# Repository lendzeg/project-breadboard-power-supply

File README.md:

# Breadboard Power Supply

This project is a breadboard power supply designed using KiCad. It provides stable and adjustable voltage outputs for prototyping and testing circuits on a breadboard. The design includes components such as voltage regulators (LM317 and LM7805), capacitors, resistors, connectors, and more.

## Features
- **Dual Voltage Outputs**:
  - Adjustable output voltage using the LM317 regulator.
  - Fixed 5V output using the LM7805 regulator.
- **Barrel Jack Input**:
  - Accepts a standard DC barrel jack for power input.
- **Screw Terminals**:
  - Easy connection for input and output wires.
- **LED Indicator**:
  - Power-on LED to indicate when the supply is active.
- **Compact Design**:
  - Optimized for use with breadboards and prototyping.

---

---

## Components List
| Reference | Value       | Footprint                                                                 |
|-----------|-------------|---------------------------------------------------------------------------|
| C1        | 10u         | Capacitor_THT:C_Disc_D3.0mm_W1.6mm_P2.50mm                                |
| C2        | 1u          | Capacitor_THT:C_Disc_D3.0mm_W1.6mm_P2.50mm                                |
| C3        | 0.1u        | Capacitor_THT:C_Disc_D3.0mm_W1.6mm_P2.50mm                                |
| D1        | LED         | LED_THT:LED_D5.0mm                                                        |
| J1        | Barrel_Jack | Connector_BarrelJack:BarrelJack_Horizontal                                |
| J2, J5    | Screw_Terminal_01x02 | TerminalBlock:TerminalBlock_bornier-2_P5.08mm                             |
| J4, J6    | Conn_01x02_Male | Connector_PinHeader_2.54mm:PinHeader_1x02_P2.54mm_Vertical                |
| J3, J7    | Conn_01x03_Male | Connector_PinHeader_2.54mm:PinHeader_1x02_P2.54mm_Vertical                |
| R2        | 330         | Resistor_THT:R_Axial_DIN0204_L3.6mm_D1.6mm_P7.62mm_Horizontal             |
| R1, R3    | 560         | Resistor_THT:R_Axial_DIN0204_L3.6mm_D1.6mm_P7.62mm_Horizontal             |
| S1        | EG1218      | digikeyfootprints:Switch_Slide_11.6x4mm_EG1218                            |
| U1        | LM317_TO-220 | Package_TO_SOT_THT:TO-220-3_Vertical                                      |
| U2        | LM7805_TO220 | Package_TO_SOT_THT:TO-220-3_Vertical                                      |

## Schematic and PCB Design
The project is designed using **KiCad**, an open-source electronics design automation (EDA) suite. The repository includes:
- Schematic files (`.sch`)
- PCB layout files (`.kicad_pcb`)
- Component libraries and footprints.

## Getting Started

### Prerequisites
- KiCad (version 6.0 or later) installed on your system.
- Basic knowledge of PCB design and soldering.

### Steps to Use
1. Clone this repository to your local machine:
   ```bash
   git clone https://github.com/lendzeg/breadboard-power-supply.git
   ```
2. Open the KiCad project file (`breadboard-power-supply.pro`) in KiCad.
3. Review the schematic and PCB layout.
4. Generate Gerber files for manufacturing or modify the design as needed.
5. Assemble the components on the PCB as per the schematic.

## License
This project is licensed under the **MIT License**. Feel free to use, modify, and distribute the design for personal or commercial purposes.

## Contributing
Contributions are welcome! If you find any issues or have suggestions for improvement, please open an issue or submit a pull request.

---

Stay Curious - Stay Hack! 😎

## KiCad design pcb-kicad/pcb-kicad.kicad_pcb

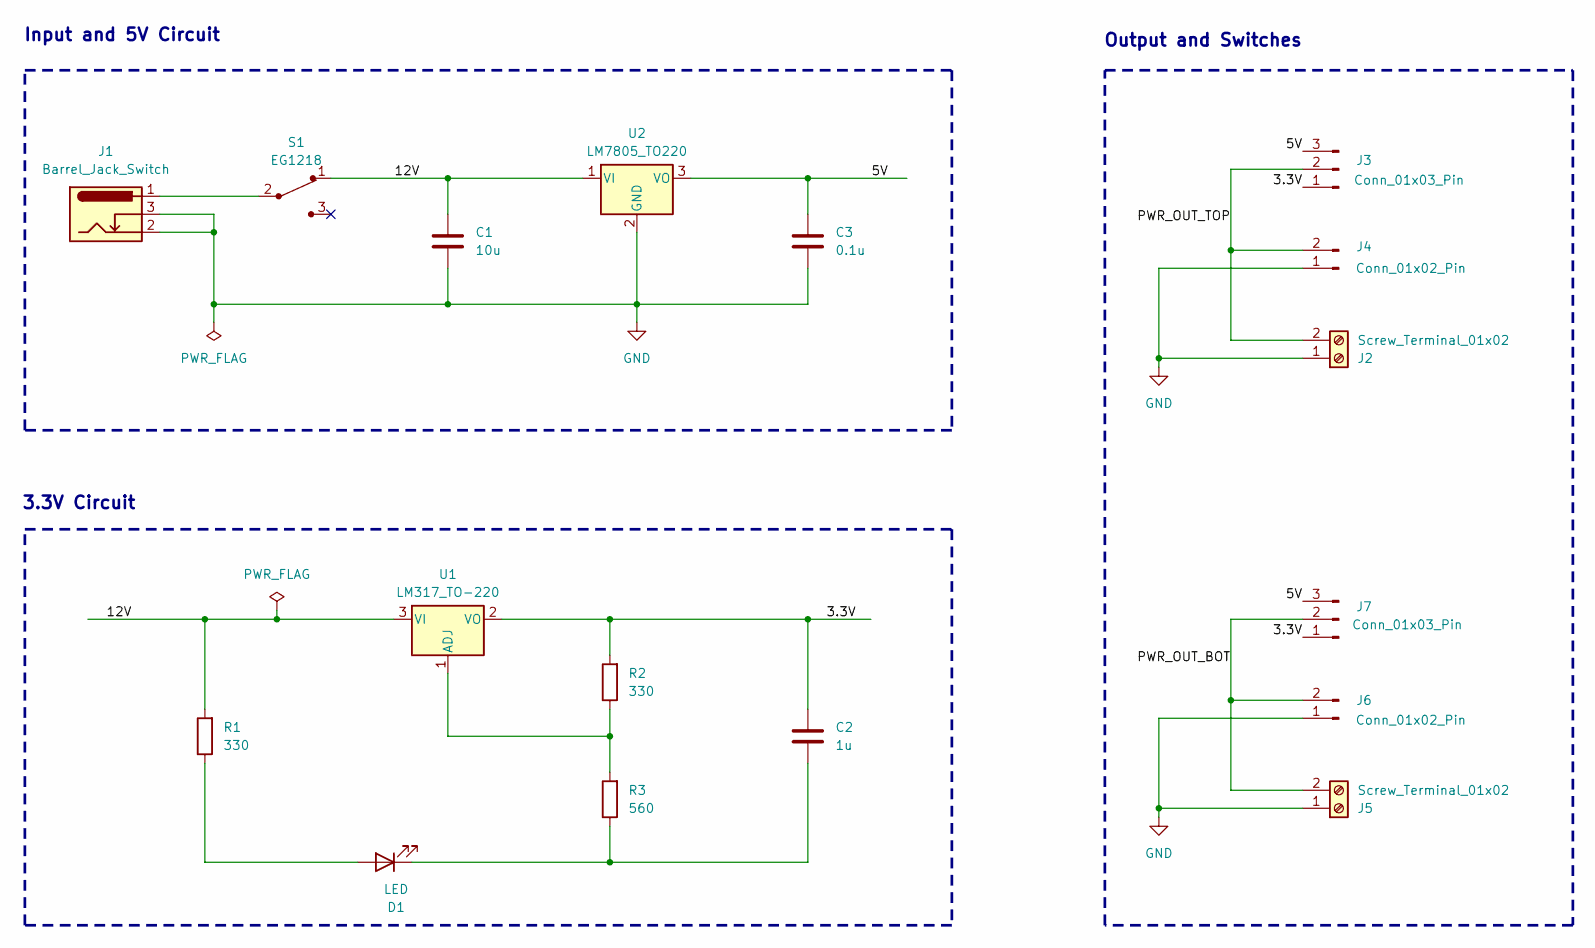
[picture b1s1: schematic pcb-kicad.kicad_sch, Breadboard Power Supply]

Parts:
C1: 10u; C_Disc_D3.0mm_W1.6mm_P2.50mm
C2: 1u; C_Disc_D3.0mm_W1.6mm_P2.50mm
C3: 0.1u; C_Disc_D3.0mm_W1.6mm_P2.50mm
D1: LED; LED_D5.0mm
J1: Barrel_Jack_Switch; BarrelJack_Horizontal
J2, J5: Screw_Terminal_01x02; TerminalBlock_bornier-2_P5.08mm
J3, J7: Conn_01x03_Pin; PinHeader_1x03_P2.54mm_Vertical
J4, J6: Conn_01x02_Pin; PinHeader_1x02_P2.54mm_Vertical
R1, R2: 330; R_Axial_DIN0204_L3.6mm_D1.6mm_P7.62mm_Horizontal
R3: 560; R_Axial_DIN0204_L3.6mm_D1.6mm_P7.62mm_Horizontal
S1: EG1218; Switch_Slide_11.6x4mm_EG1218; MPN EG1218; Digi-Key_PN EG1903-ND
U1: LM317_TO-220; TO-220-3_Vertical
U2: LM7805_TO220; TO-220-3_Vertical

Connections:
/3.3V: C2.1, J3.1, J7.1, R2.2, U1.2 (VO)
/5V: C3.1, J3.3, J7.3, U2.3 (VO)
/12V: C1.1, R1.2, S1.1, U1.3 (VI), U2.1 (VI)
/PWR_OUT_BOT: J5.2, J6.2, J7.2
/PWR_OUT_TOP: J2.2, J3.2, J4.2
GND: C1.2, C3.2, J1.2, J1.3, J2.1, J4.1, J5.1, J6.1, U2.2 (GND)
unnamed: D1.2 (A), R1.1
unnamed: C2.2, D1.1 (K), R3.1
unnamed: J1.1, S1.2
unnamed: R2.1, R3.2, U1.1 (ADJ)

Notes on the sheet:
3.3V Circuit
Output and Switches
Input and 5V Circuit

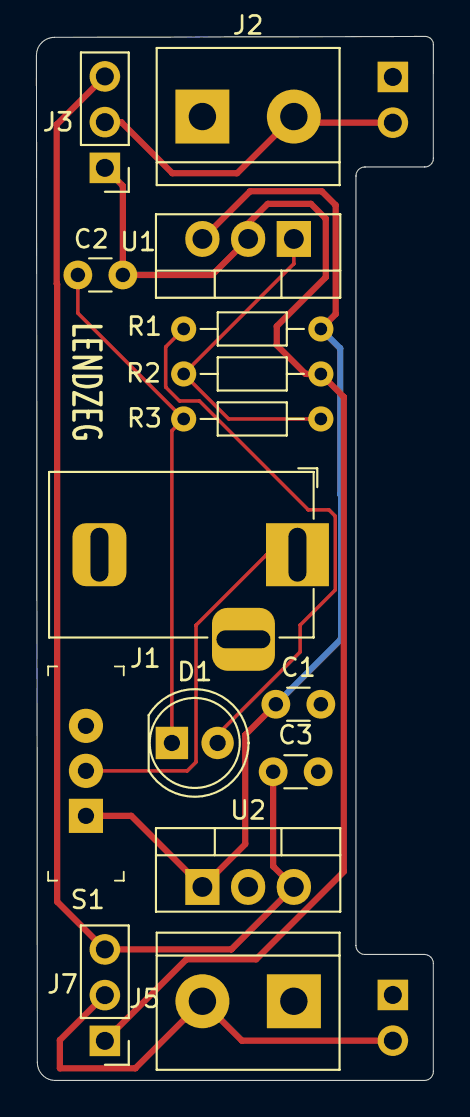
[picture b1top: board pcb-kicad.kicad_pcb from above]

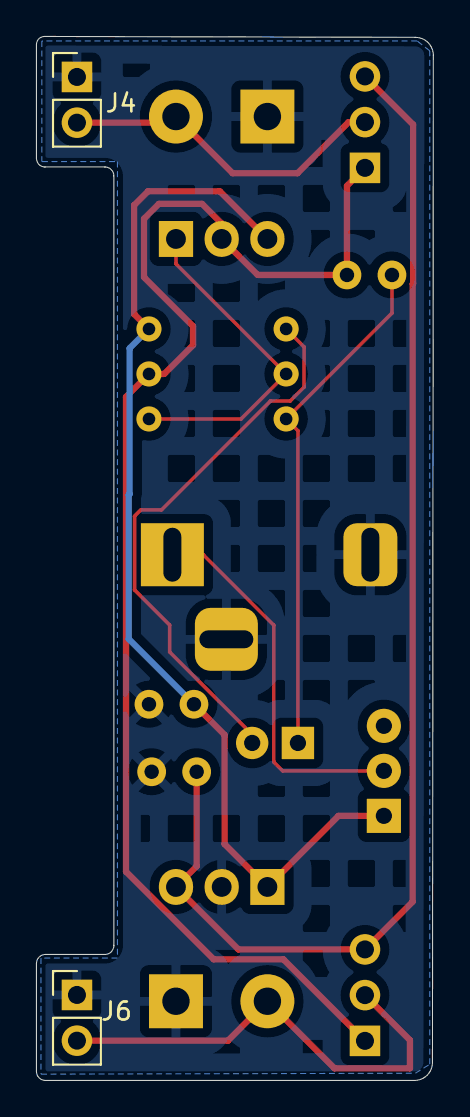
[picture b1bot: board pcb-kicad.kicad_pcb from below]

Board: 2 copper layers, 22.1 x 58.0 mm, 17 parts (2 on the bottom side), 10 nets.

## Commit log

2025-03-19 README updated. Kicad project created. Symbols and footprints associated.
2025-03-24 Schematic completed. Connections, nets, net classes, comments added.
2025-03-27 First prototype finished.

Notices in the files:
README.md:
License: MIT
